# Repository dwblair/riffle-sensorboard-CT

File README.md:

# riffle-sensorboard-CT
conductivity and temperature

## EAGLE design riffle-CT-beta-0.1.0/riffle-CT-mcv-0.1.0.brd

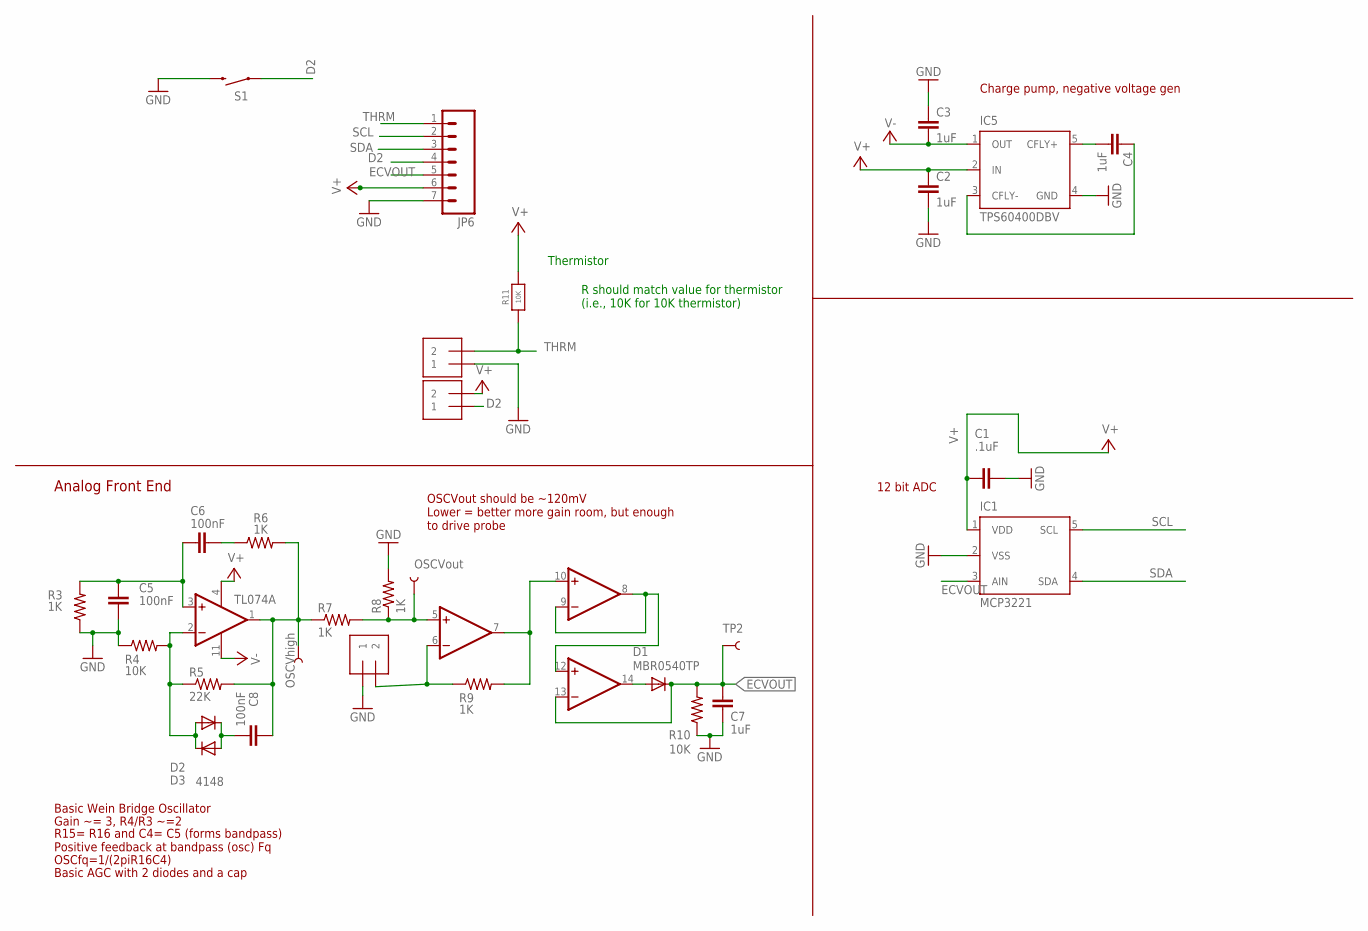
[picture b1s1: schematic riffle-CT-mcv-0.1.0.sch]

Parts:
1W: 1X2-3.5MM
C1: .1uF; 0805
C2, C3, C4, C7: 1uF; 0805
C5, C6, C8: 100nF; 0805
D1: MBR0540TP; SOD123
D2, D3: 4148; SOD123
EC: 1X2-3.5MM
IC1: MCP3221; SOT23-DBV
IC5: TPS60400DBV; SOT23-DBV
JP6: M07; 1X07
R3, R6, R7, R8, R9: 1K; 0805
R4, R10: 10K; 0805
R5: 22K; 0805
R11: 10K; 0603-NO
S1: REED; REED_SWITCH_PLASTIC
THRM: 1X2-3.5MM
TL074: TL074; SO14
TP2: TEST-POINT3; PAD.03X.03
TP3: OSCVhigh; PAD.03X.03
TP5: OSCVout; PAD.03X.03

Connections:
D2: 1W.1, JP6.4, S1.P$1 (1)
ECVOUT: C7.2, D1.C, IC1.3 (AIN), JP6.5, R10.2, TL074.13 (-IN), TP2.P$1
GND: C1.1, C2.2, C3.1, C5.1, C7.1, EC.1, IC1.2 (VSS), IC5.4 (GND), JP6.7, R3.1, R4.1, R8.2, R10.1, S1.P$2 (2), THRM.1
unnamed: C8.2, D2.C, D3.A
unnamed: C4.1, IC5.3 (CFLY-)
unnamed: C4.2, IC5.5 (CFLY+)
unnamed: C5.2, C6.2, R3.2, TL074.3 (+IN)
unnamed: D2.A, D3.C, R4.2, R5.1, TL074.2 (-IN)
unnamed: C6.1, R6.1
unnamed: C8.1, R5.2, R6.2, R7.1, TL074.1 (OUT), TP3.P$1
unnamed: R7.2, R8.1, TL074.5 (+IN), TP5.P$1
unnamed: EC.2, R9.1, TL074.6 (-IN)
unnamed: R9.2, TL074.7 (OUT), TL074.10 (+IN)
unnamed: TL074.8 (OUT), TL074.9 (-IN), TL074.12 (+IN)
unnamed: D1.A, TL074.14 (OUT)
SCL: IC1.5 (SCL), JP6.2
SDA: IC1.4 (SDA), JP6.3
THRM: JP6.1, R11.1, THRM.2
V+: 1W.2, C1.2, C2.1, IC1.1 (VDD), IC5.2 (IN), JP6.6, R11.2, TL074.4 (V+)
V-: C3.2, IC5.1 (OUT), TL074.11 (V-)

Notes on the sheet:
12 bit ADC
Charge pump, negative voltage gen
Analog Front End
Basic Wein Bridge Oscillator
Gain ~= 3, R4/R3 ~=2
R15= R16 and C4= C5 (forms bandpass) Positive feedback at bandpass (osc) Fq
OSCfq=1/(2piR16C4)
Basic AGC with 2 diodes and a cap
OSCVout should be ~120mV Lower = better more gain room, but enough to drive probe
Thermistor
R should match value for thermistor (i.e., 10K for 10K thermistor)

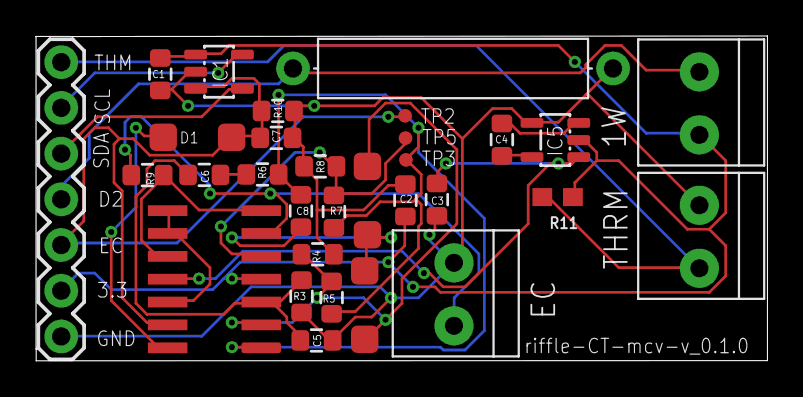
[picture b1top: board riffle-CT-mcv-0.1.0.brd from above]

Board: 2 copper layers, 40.6 x 18.0 mm, 31 parts (0 on the bottom side), 20 nets.

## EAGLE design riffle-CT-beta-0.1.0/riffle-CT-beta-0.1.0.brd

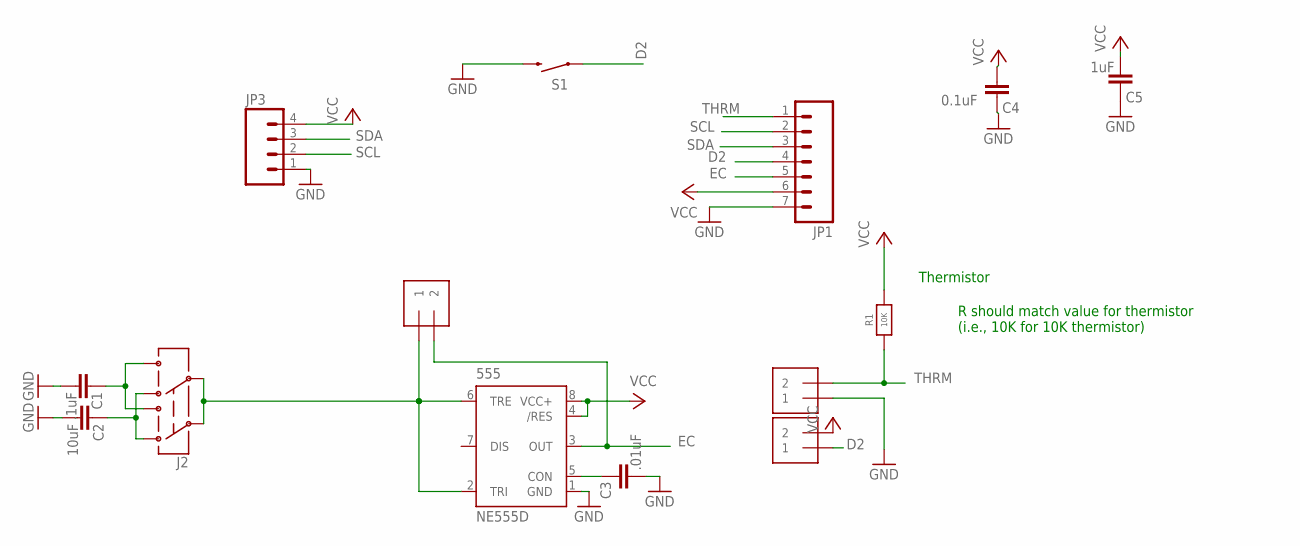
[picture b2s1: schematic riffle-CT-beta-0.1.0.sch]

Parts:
1W: 1X2-3.5MM
555: NE555D; SO08@1
C1: .1uF; 0603-CAP
C2: 10uF; 0603-CAP
C3: .01uF; 0603-CAP
C4: 0.1uF; 0603-CAP
C5: 1uF; 0603-CAP
EC: 1X2-3.5MM
J2: AYZ0202
JP1: M07; 1X07
JP3: M04SMD; 1X04-SMD
R1: 10K; 0603-NO
S1: REED; REED_SWITCH_PLASTIC
THRM: 1X2-3.5MM

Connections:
D2: 1W.1, JP1.4, S1.P$1 (1)
EC: 555.3 (OUT), EC.2, JP1.5
GND: 555.1 (GND), C1.1, C2.1, C3.1, C4.2, C5.2, JP1.7, JP3.1, S1.P$2 (2), THRM.1
N1: 555.2 (TRI), 555.6 (TRE), EC.1, J2.2, J2.5
unnamed: 555.5 (CON), C3.2
unnamed: C2.2, J2.3 (1), J2.6 (4)
SCL: JP1.2, JP3.2
SDA: JP1.3, JP3.3
THRM: JP1.1, R1.1, THRM.2
VCC: 1W.2, 555.4 (/RES), 555.8 (VCC+), C4.1, C5.1, JP1.6, JP3.4, R1.2
VDD2: C1.2, J2.1 (3), J2.4 (6)

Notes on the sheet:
Thermistor
R should match value for thermistor (i.e., 10K for 10K thermistor)

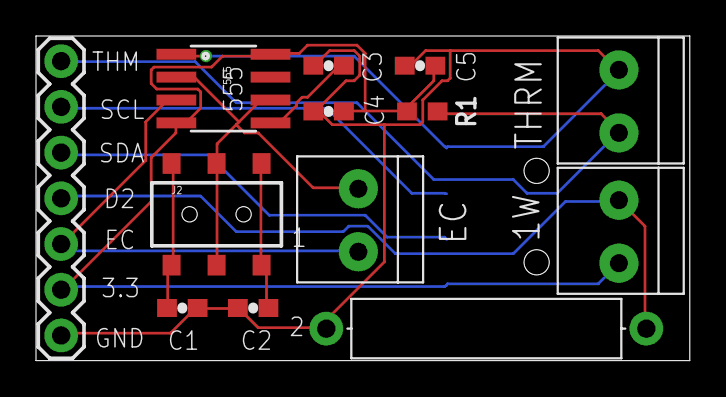
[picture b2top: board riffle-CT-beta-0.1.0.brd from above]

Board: 2 copper layers, 36.3 x 18.0 mm, 14 parts (1 on the bottom side), 11 nets.

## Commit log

2016-01-15 optimized layout of parts

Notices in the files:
riffle-CT-beta-0.1.0/riffle-CT-beta-0.1.0.brd:
CERN OHL v1.2
parts and their libraries:
SparkFun-AnalogIC: Licensing:Creative Commons ShareAlike 4.0 International - https://creativecommons.org/licenses/by-sa/4.0
microbuilder: This work is placed in the public domain, and may be freely used for commercial and non-commercial work with the following conditions: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
